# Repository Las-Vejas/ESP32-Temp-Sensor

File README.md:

# ESP32-Temp-Sensor

This is a temperature sensor comprised of a Seeed Xiao ESP32-C6, a HDC1080DMBR temperature and humidity sensor and an OLED display.

I made the PCB in 2 hrs and tried to compact everything as well as possible.

## Pictures of PCB & Schematic

### PCB front

### PCB back

### PCB

### Schematic

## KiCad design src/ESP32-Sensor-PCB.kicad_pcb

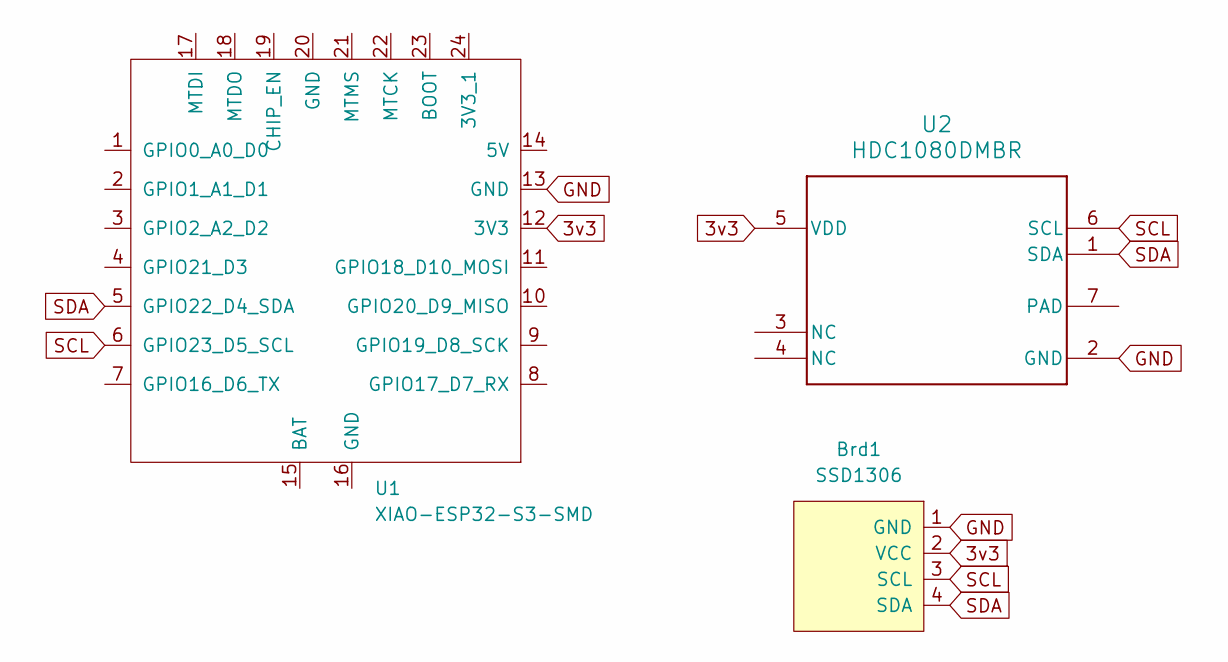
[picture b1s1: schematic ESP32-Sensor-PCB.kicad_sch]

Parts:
Brd1: SSD1306; 128x64OLED
U1: XIAO-ESP32-S3-SMD; XIAO-ESP32C6-DIP
U2: HDC1080DMBR; DMB0006A

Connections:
3v3: Brd1.2 (VCC), U1.12 (3V3), U2.5 (VDD)
GND: Brd1.1 (GND), U1.13 (GND), U2.2 (GND)
SCL: Brd1.3 (SCL), U1.6 (GPIO23_D5_SCL), U2.6 (SCL)
SDA: Brd1.4 (SDA), U1.5 (GPIO22_D4_SDA), U2.1 (SDA)

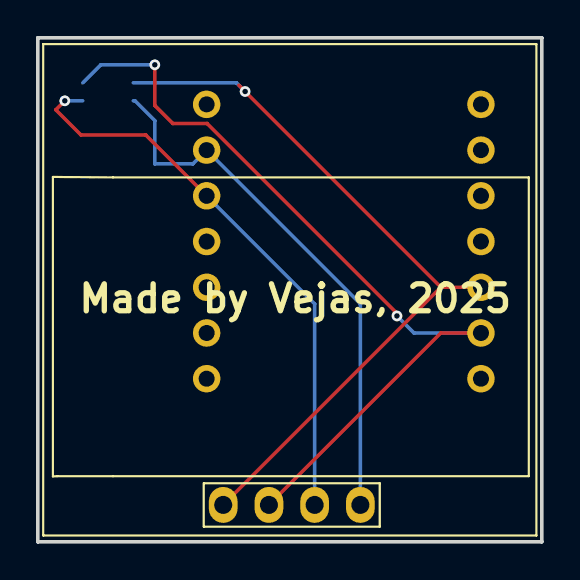
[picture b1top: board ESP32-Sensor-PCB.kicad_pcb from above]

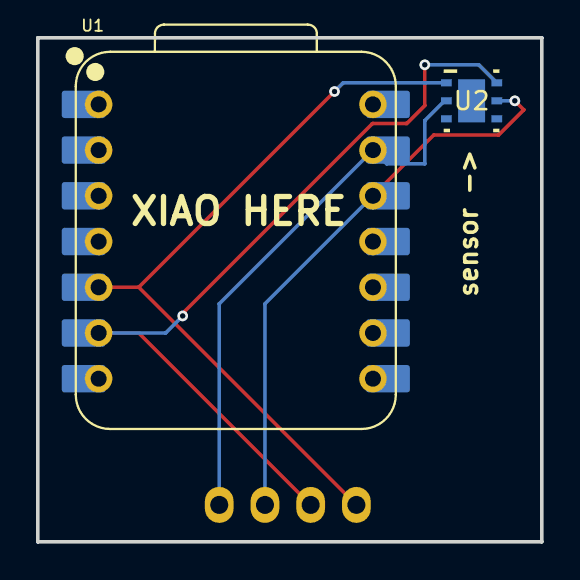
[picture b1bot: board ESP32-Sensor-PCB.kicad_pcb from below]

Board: 2 copper layers, 28.0 x 28.0 mm, 3 parts (2 on the bottom side), 4 nets.

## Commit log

2025-08-29 init
2025-08-29 v1.1
2025-08-29 v1.2
2025-09-05 Update Journal.md
    Added pcb images
2025-09-07 stupid me
